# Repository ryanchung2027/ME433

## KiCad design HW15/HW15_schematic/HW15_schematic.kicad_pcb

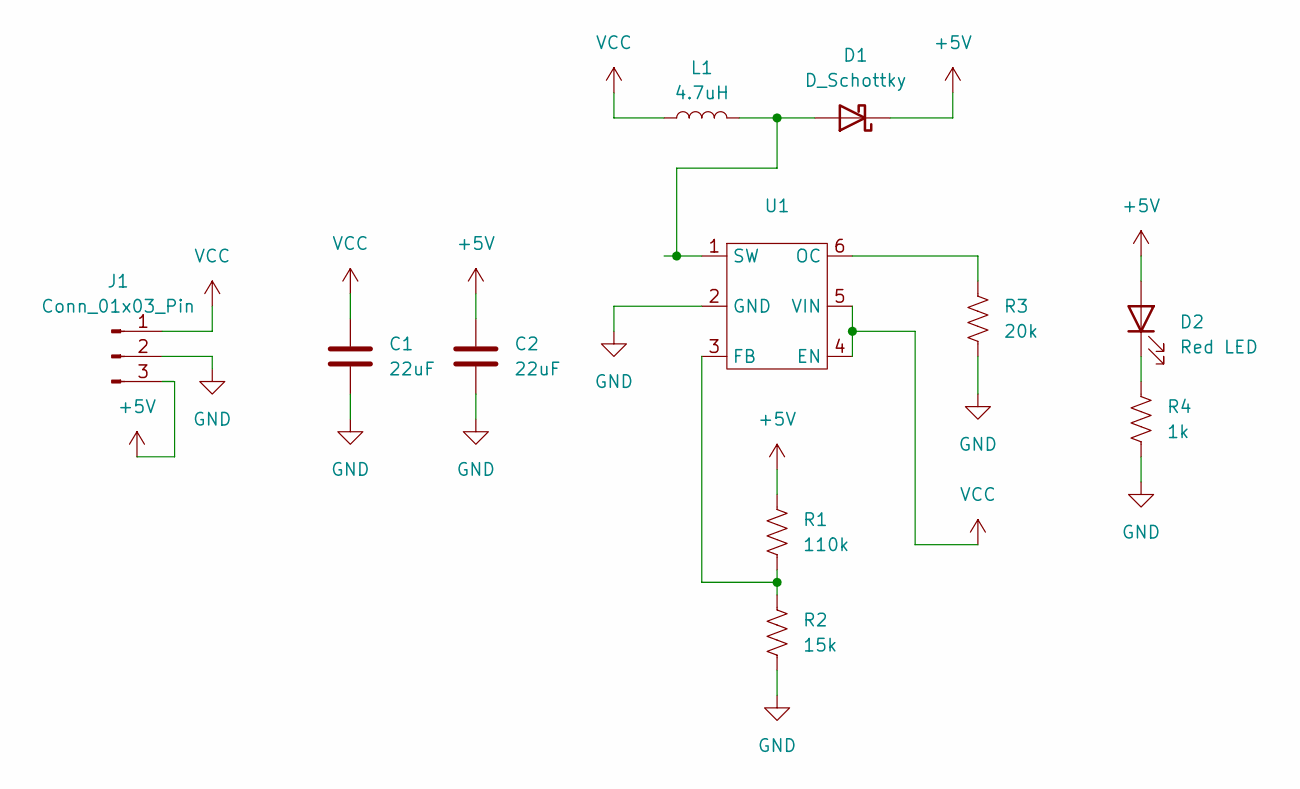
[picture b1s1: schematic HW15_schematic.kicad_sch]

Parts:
C1, C2: 22uF
D1: D_Schottky
D2: Red LED
J1: Conn_01x03_Pin
L1: 4.7uH
R1: 110k
R2: 15k
R3: 20k
R4: 1k
U1: (no value)

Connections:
+5V: C2.1, D1.1 (K), D2.2 (A), J1.3, R1.1
GND: C1.2, C2.2, J1.2, R2.2, R3.2, R4.2, U1.2 (GND)
unnamed: D1.2 (A), L1.2, U1.1 (SW)
unnamed: D2.1 (K), R4.1
unnamed: R1.2, R2.1, U1.3 (FB)
unnamed: R3.1, U1.6 (OC)
VCC: C1.1, J1.1, L1.1, U1.4 (EN), U1.5 (VIN)

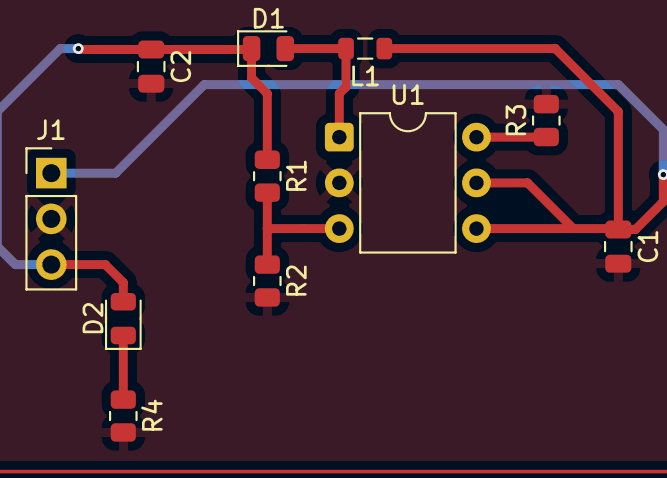
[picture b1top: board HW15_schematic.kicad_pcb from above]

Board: 2 copper layers, 11 parts (0 on the bottom side), 7 nets.

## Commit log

2025-04-11 Forgot to push earlier (sorry) but includes completed HW2 and miscellaneous sample files
2025-04-11 made hw3 file and also added some comments to HW2
2025-04-11 added led functions from blink and the example code from the HW3 Git page
2025-04-11 renamed HW3 to HW3_code
2025-04-11 renamed HW3 folder into HW3_code
2025-04-11 edited makelists to accomodate changed folder/file names and got rid of uneccessary code that was copy pasted
2025-04-11 added adc initialization
2025-04-11 fixed initialization errors for adc hardware library and edited interrupt to prompt user
2025-04-11 added nested for loop and reading adc value
2025-04-15 finished hw_3 code
2025-04-15 started HW4
2025-04-16 started data_write function
2025-04-20 made a function to get the value of a sine wave with amplitude 1.65 centered around 1.65
2025-04-22 finished homework 4!
2025-04-22 added photo of oscilloscope trace
2025-04-22 created hw 5 and added sample code from assignment
2025-04-22 calculated cycles for addition
2025-04-22 added the same code for addition to subtraction, multiplication and division
2025-04-22 commented out math + timing code and added functions from hw4
2025-04-22 wrote spi_ram_init and created hw 7 files
2025-04-22 forgot to put function declarations at the top of the file
2025-04-22 finished ram_data_write
2025-04-22 finished ram_data_read
2025-04-22 added data write from hw4 and added more code to main
2025-04-22 forgot declaration for ram_data_read at top of file
2025-04-22 troubleshot code and finished hw5
2025-04-22 added oscilloscope ss
2025-04-22 replaced oscilloscope screenshot with a png instead of HEIC
2025-05-05 created HW6 folder and files
2025-06-03 Finished HW6
2025-06-03 included ssd1306 and font header files into hw7 file + started code
2025-06-03 started hw7
2025-06-03 got led and screen pixel blinking
2025-06-03 made drawChar function
2025-06-03 made the drawMessage function
2025-06-03 extraneous changes
2025-06-03 added adc functionality
2025-06-03 made HW8 folder and c file
2025-06-03 finished hw 8
2025-06-03 Finished HW9
2025-06-04 Finished hw10
2025-06-09 finished hw11
2025-06-09 got rid of extra hw11.c file
2025-06-09 finished hw14
2025-06-09 finished HW15
2025-06-09 finished hw16
